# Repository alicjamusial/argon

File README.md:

# Argon & Benzene - SPI NOR Flash programmer & reader

### ◾ About the project

This project consists of two boards: **Argon** and **Benzene**.

 **Argon** is a SPI NOR flash programmer & reader. It's based on the FT2232H microcontroller (with two UARTs - A & B). The board has three LED indicators of data - on TX, RX and CS lines and some sockets to be able to plug in the logic analyzer. Version 1.0 of Argon is available [in the releases section](https://github.com/alicjamusial/argon/releases/tag/argon-1.0). 

<br>

 **Benzene** is a DIP-8/DIP-16 to Argon adapter. It includes mostly a few capacitors and resistors to allow SPI flash to run smoothly. There is also a 555 timer with LED indicator on CS line goldpins to attach the logic analyzer.
Version 1.0 of Benzene is available [in the releases section](https://github.com/alicjamusial/argon/releases/tag/benzene-1.0).

<br>
Argon works best with Benzene attached - they are designed to match each other (you can put two Benzene boards on top of the Argon). Argon can be also used separately as USB<->UART/FIFO/I2C/SPI converter (similar to FTDI Mini Module). 

Both boards were designed using [KiCad 5.1.6](https://kicad.org/).

### ◾ Software
Argon software is available in [this repository](https://github.com/alicjamusial/argon-driver).

### ◾ Known issues
**Argon 1.1**
- No known issues, but wasn't assembled yet.

**Benzene 1.0**
- Logo is too small and illegible (not very important, so won't be fixed by now)

**Project**
- KiCad libraries are a bit chaotic (not very important, so won't be fixed by now)

### ◾ Usage examples

Argon is meant to be used as SPI NOR flash reader & writer with:
- Benzene & flash soldered to DIP-8/DIP-16 board adapter
- Benzene & flash inside DIP-8/DIP-16 adapter
- Benzene & clip with DIP-8/16 adapter to read or program flash placed on another board

It can be also used standalone as USB<->UART/FIFO/I2C/SPI converter (all FTDI Mini Module functionalities in the nicer and more readable form).

Note: all photos show Argon in version 1.0.

### ◾ Schematics and designs
All of them can be found [in the releases section](https://github.com/alicjamusial/argon/releases) as KiCad files, gerber files, pdf and svg format.

#### ▪️ Argon 1.1

#### ▪️ Benzene 1.0

### ◾ Other hints
When assembling your own Argon or Benzene please use LED's resistors calculated for your chosen colours.

### ◾ License
Argon and Benzene are available on Creative Commons Attribution Share Alike 4.0 International license (more in [license file](LICENSE.txt)). You are free to use it, modify it and produce as many of your own boards as you need :)

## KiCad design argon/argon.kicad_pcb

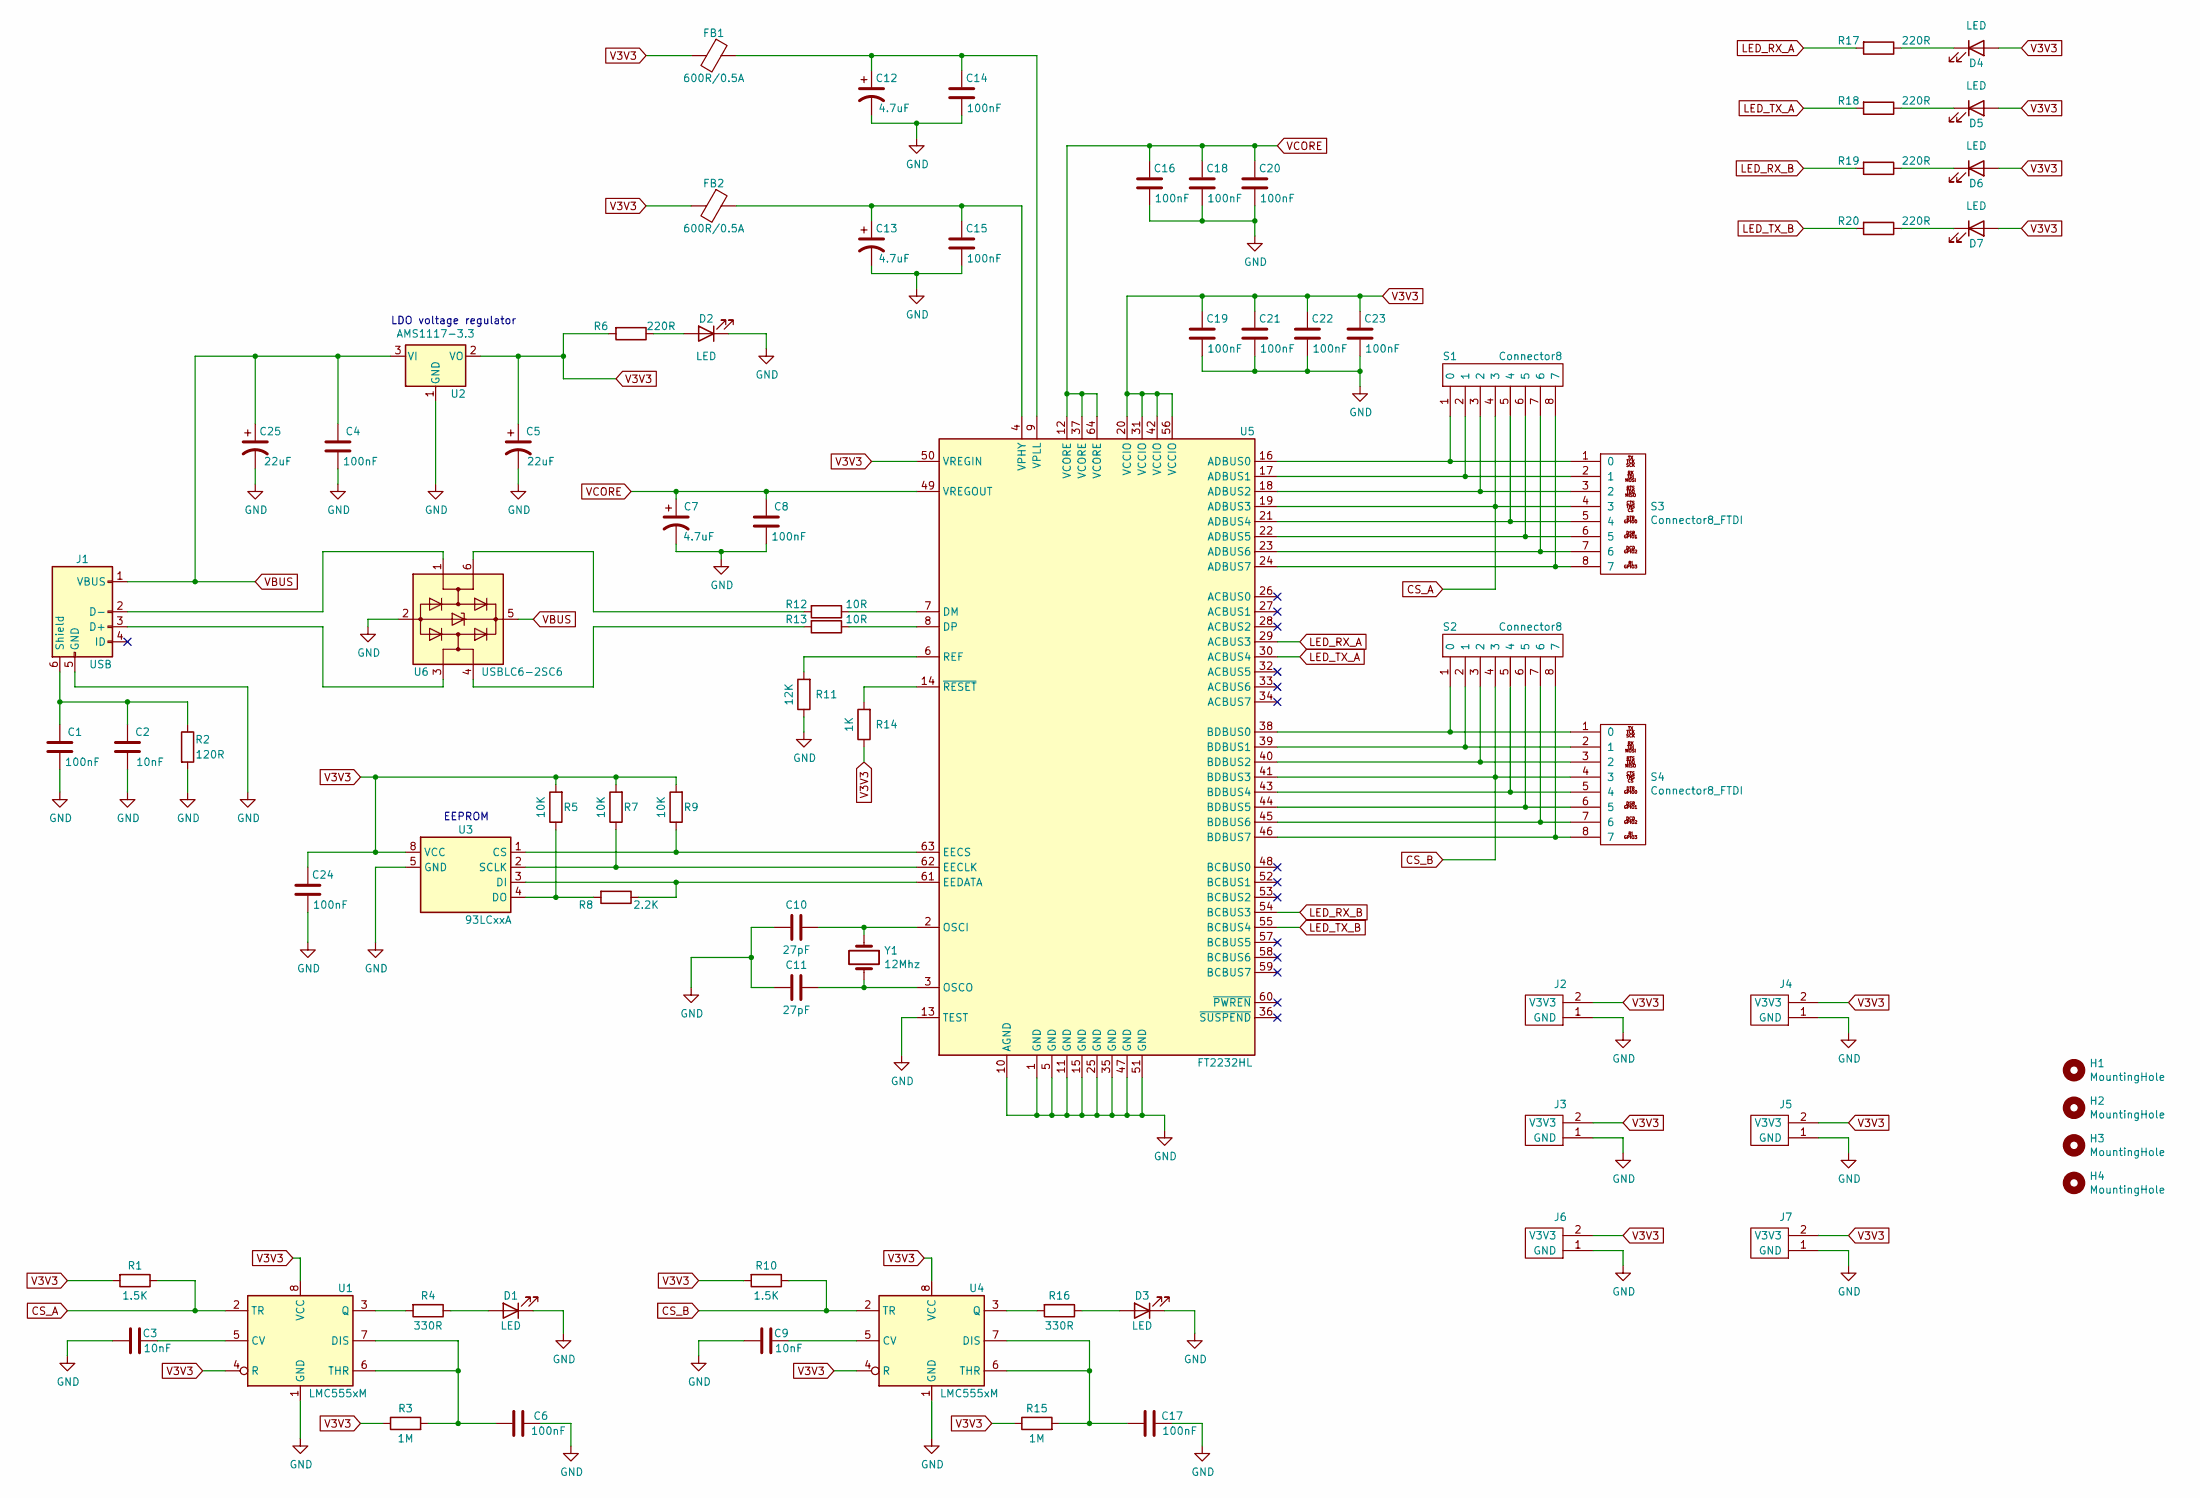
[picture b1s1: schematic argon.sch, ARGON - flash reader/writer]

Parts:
C1, C4, C6, C8, C14, C15, C16, C17, C18, C19, C20, C21, C22, C23, C24: 100nF; C_0603_1608Metric
C2, C3, C9: 10nF; C_0603_1608Metric
C5, C25: 22uF; CP_EIA-3216-18_Kemet-A
C7, C12, C13: 4.7uF; CP_EIA-3216-18_Kemet-A
C10, C11: 27pF; C_0603_1608Metric
D1, D2, D3, D4, D5, D6, D7: LED; LED_0805_2012Metric
FB1, FB2: 600R/0.5A; Murata-BLM18-0.15-t0.8-0-0-IPC_A
H1, H2, H3, H4: MountingHole; MountingHole_3.2mm_M3
J1: USB; USB_Mini-B_Wuerth_65100516121_Horizontal
J2, J3, J4, J5, J6, J7: V3V3-GND; PinHeader_1x02_P2.54mm_Vertical
R1, R10: 1.5K; R_0603_1608Metric
R2: 120R; R_0603_1608Metric
R3, R15: 1M; R_0603_1608Metric
R4, R16: 330R; R_0603_1608Metric
R5, R7, R9: 10K; R_0603_1608Metric
R6, R17, R18, R19, R20: 220R; R_0603_1608Metric
R8: 2.2K; R_0603_1608Metric
R11: 12K; R_0603_1608Metric
R12, R13: 10R; R_0603_1608Metric
R14: 1K; R_0603_1608Metric
S1, S2: Connector8; PinHeader_1x08_P2.54mm_Vertical
S3, S4: Connector8_FTDI; PinHeader_1x08_P2.54mm_Vertical
U1, U4: LMC555xM; VSSOP-8_3.0x3.0mm_P0.65mm
U2: AMS1117-3.3; SOT-223-3_TabPin2
U3: 93LCxxA; SOIC-8_3.9x4.9mm_P1.27mm
U5: FT2232HL; LQFP-64_10x10mm_P0.5mm
U6: USBLC6-2SC6; SOT-23-6
Y1: 12Mhz; Crystal_SMD_SeikoEpson_TSX3225-4Pin_3.2x2.5mm

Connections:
CS_A: R1.1, S1.4 (3), S3.4 (3), U1.2 (TR), U5.19 (ADBUS3)
CS_B: R10.1, S2.4 (3), S4.4 (3), U4.2 (TR), U5.41 (BDBUS3)
GND: C1.1, C2.1, C3.2, C4.2, C5.2, C6.2, C7.2, C8.1, C9.2, C10.2, C11.2, C12.2, C13.2, C14.1, C15.1, C16.1, C17.2, C18.1, C19.1, C20.1, C21.1, C22.1, C23.1, C24.1, C25.2, D1.1 (K), D2.1 (K), D3.1 (K), J1.5 (GND), J2.1 (GND), J3.1 (GND), J4.1 (GND), J5.1 (GND), J6.1 (GND), J7.1 (GND), R2.2, R11.1, U1.1 (GND), U2.1 (GND), U3.5 (GND), U4.1 (GND), U5.1 (GND), U5.5 (GND), U5.10 (AGND), U5.11 (GND), U5.13 (TEST), U5.15 (GND), U5.25 (GND), U5.35 (GND), U5.47 (GND), U5.51 (GND), U6.2 (GND)
LED_RX_A: R17.2, U5.29 (ACBUS3)
LED_RX_B: R19.2, U5.54 (BCBUS3)
LED_TX_A: R18.2, U5.30 (ACBUS4)
LED_TX_B: R20.2, U5.55 (BCBUS4)
unnamed: C1.2, C2.2, J1.6 (Shield), R2.1
unnamed: C3.1, U1.5 (CV)
unnamed: C6.1, R3.2, U1.6 (THR), U1.7 (DIS)
unnamed: C9.1, U4.5 (CV)
unnamed: C10.1, U5.2 (OSCI), Y1.1
unnamed: C11.1, U5.3 (OSCO), Y1.2
unnamed: C12.1, C14.2, FB1.1, U5.9 (VPLL)
unnamed: C13.1, C15.2, FB2.1, U5.4 (VPHY)
unnamed: C17.1, R15.2, U4.6 (THR), U4.7 (DIS)
unnamed: D1.2 (A), R4.1
unnamed: D2.2 (A), R6.1
unnamed: D3.2 (A), R16.1
unnamed: D4.1 (K), R17.1
unnamed: D5.1 (K), R18.1
unnamed: D6.1 (K), R19.1
unnamed: D7.1 (K), R20.1
unnamed: J1.2 (D-), U6.1 (I/O1)
unnamed: J1.3 (D+), U6.3 (I/O2)
unnamed: R4.2, U1.3 (Q)
unnamed: R5.1, R8.2, U3.4 (DO)
unnamed: R7.1, U3.2 (SCLK), U5.62 (EECLK)
unnamed: R8.1, U3.3 (DI), U5.61 (EEDATA)
unnamed: R9.1, U3.1 (CS), U5.63 (EECS)
unnamed: R11.2, U5.6 (REF)
unnamed: R12.1, U5.7 (DM)
unnamed: R12.2, U6.6 (I/O1)
unnamed: R13.1, U5.8 (DP)
unnamed: R13.2, U6.4 (I/O2)
unnamed: R14.2, U5.14 (~RESET)
unnamed: R16.2, U4.3 (Q)
unnamed: S1.1 (0), S3.1 (0), U5.16 (ADBUS0)
unnamed: S1.2 (1), S3.2 (1), U5.17 (ADBUS1)
unnamed: S1.3 (2), S3.3 (2), U5.18 (ADBUS2)
unnamed: S1.5 (4), S3.5 (4), U5.21 (ADBUS4)
unnamed: S1.6 (5), S3.6 (5), U5.22 (ADBUS5)
unnamed: S1.7 (6), S3.7 (6), U5.23 (ADBUS6)
unnamed: S1.8 (7), S3.8 (7), U5.24 (ADBUS7)
unnamed: S2.1 (0), S4.1 (0), U5.38 (BDBUS0)
unnamed: S2.2 (1), S4.2 (1), U5.39 (BDBUS1)
unnamed: S2.3 (2), S4.3 (2), U5.40 (BDBUS2)
unnamed: S2.5 (4), S4.5 (4), U5.43 (BDBUS4)
unnamed: S2.6 (5), S4.6 (5), U5.44 (BDBUS5)
unnamed: S2.7 (6), S4.7 (6), U5.45 (BDBUS6)
unnamed: S2.8 (7), S4.8 (7), U5.46 (BDBUS7)
V3V3: C5.1, C19.2, C21.2, C22.2, C23.2, C24.2, D4.2 (A), D5.2 (A), D6.2 (A), D7.2 (A), FB1.2, FB2.2, J2.2 (V3V3), J3.2 (V3V3), J4.2 (V3V3), J5.2 (V3V3), J6.2 (V3V3), J7.2 (V3V3), R1.2, R3.1, R5.2, R6.2, R7.2, R9.2, R10.2, R14.1, R15.1, U1.4 (R), U1.8 (VCC), U2.2 (VO), U3.8 (VCC), U4.4 (R), U4.8 (VCC), U5.20 (VCCIO), U5.31 (VCCIO), U5.42 (VCCIO), U5.50 (VREGIN), U5.56 (VCCIO)
VBUS: C4.1, C25.1, J1.1 (VBUS), U2.3 (VI), U6.5 (VBUS)
VCORE: C7.1, C8.2, C16.2, C18.2, C20.2, U5.12 (VCORE), U5.37 (VCORE), U5.49 (VREGOUT), U5.64 (VCORE)

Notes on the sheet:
LDO voltage regulator
EEPROM

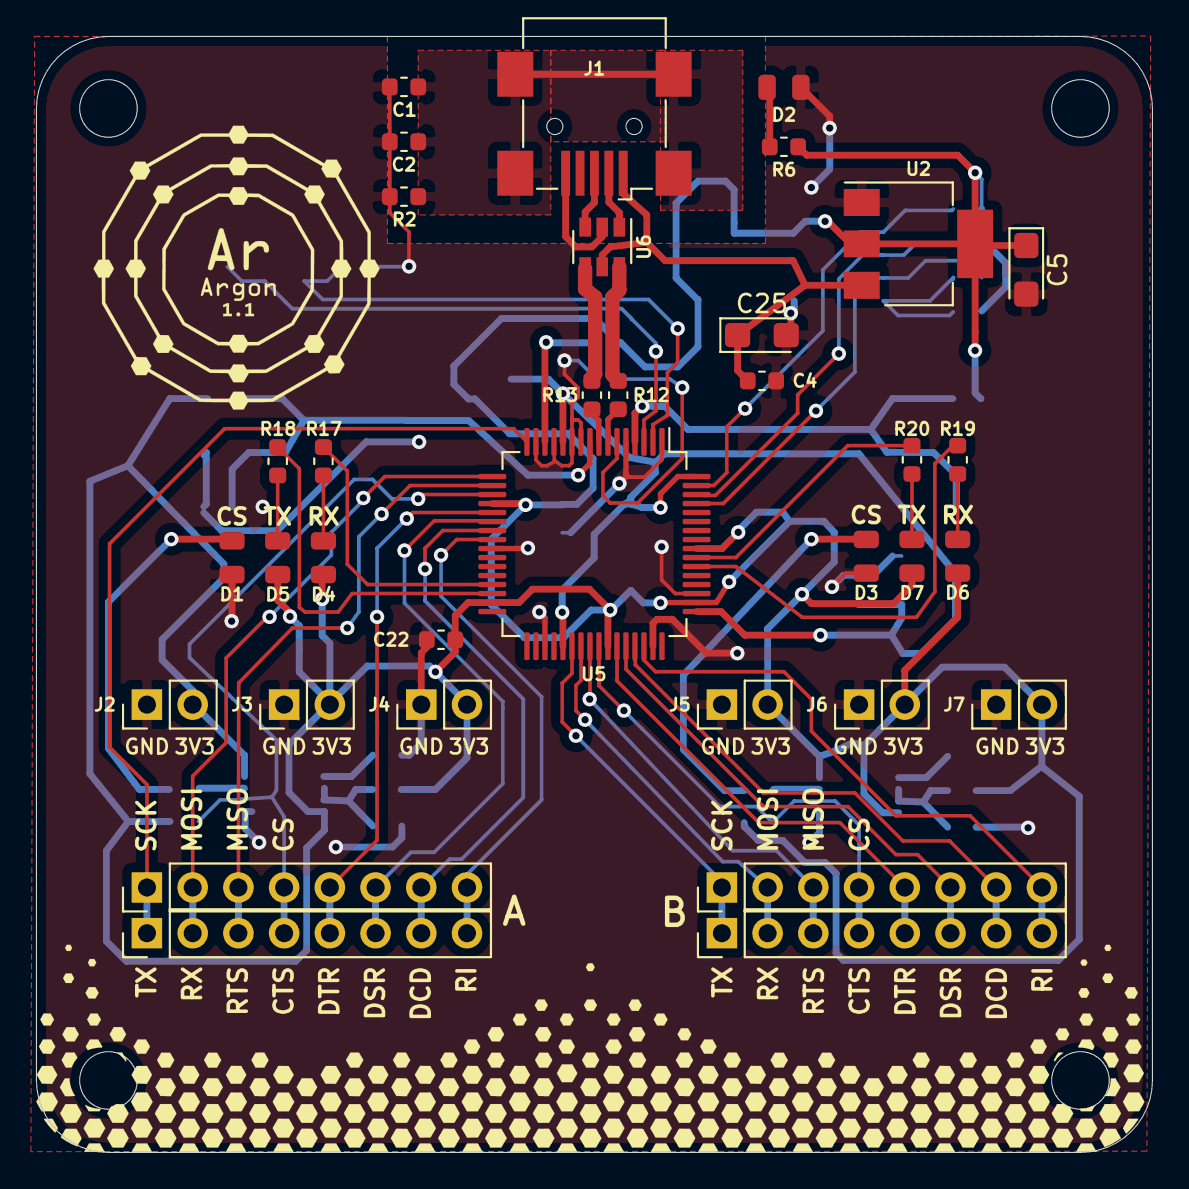
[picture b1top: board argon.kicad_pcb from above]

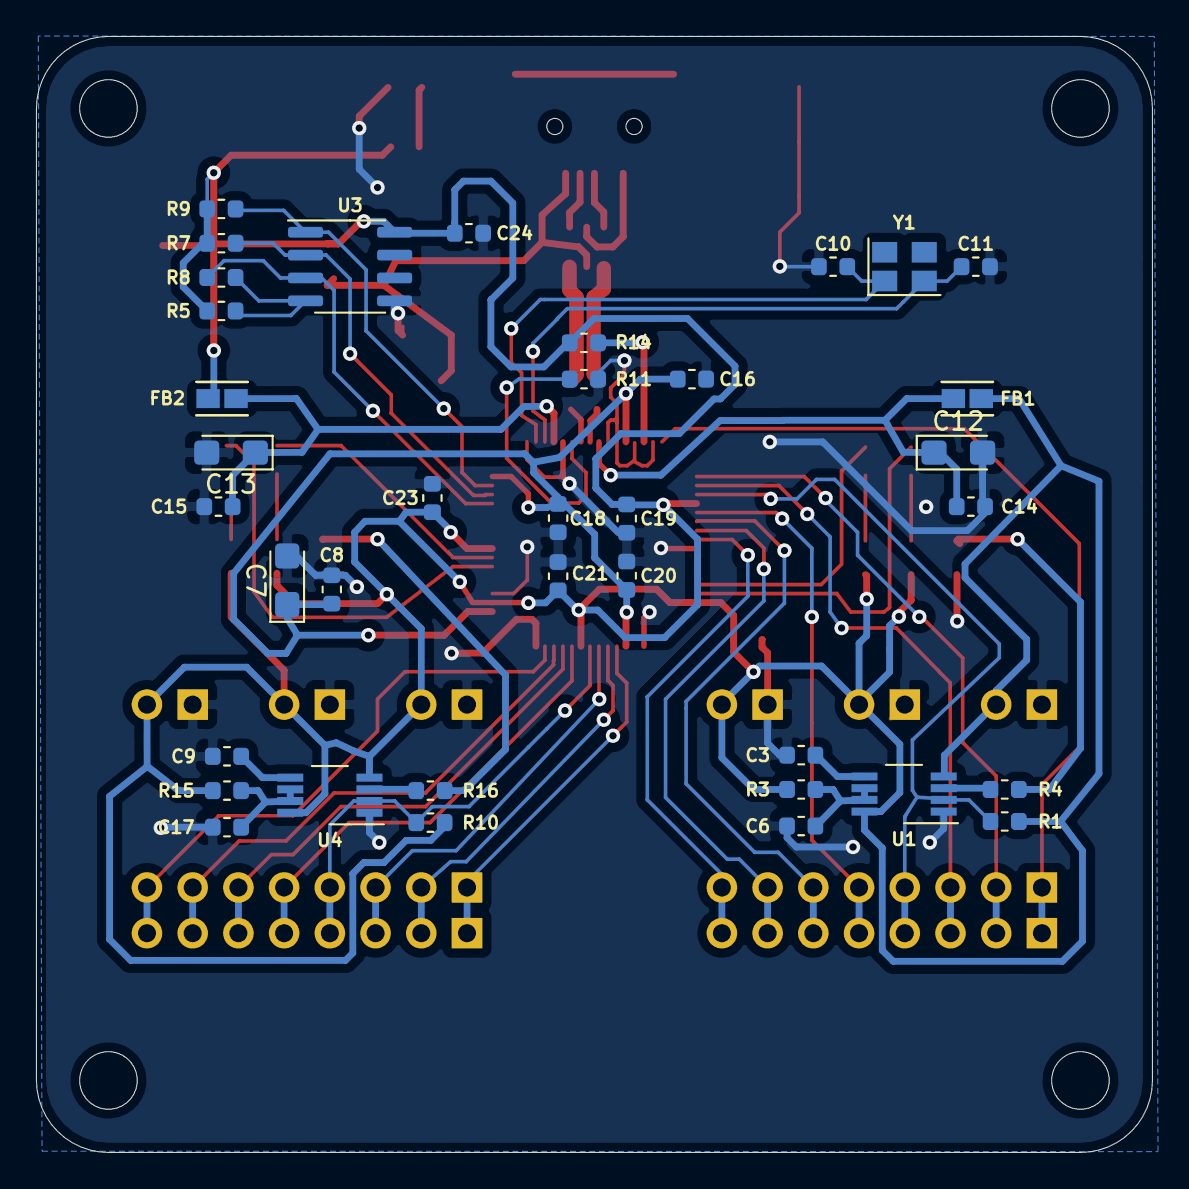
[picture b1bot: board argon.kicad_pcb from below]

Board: 2 copper layers, 62.0 x 62.0 mm, 76 parts (37 on the bottom side), 54 nets.

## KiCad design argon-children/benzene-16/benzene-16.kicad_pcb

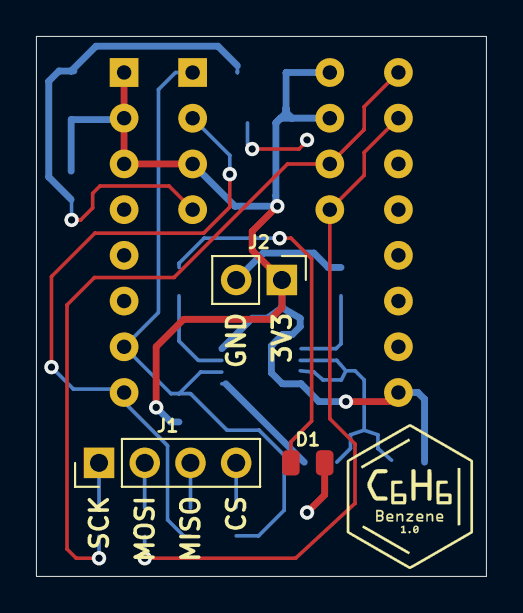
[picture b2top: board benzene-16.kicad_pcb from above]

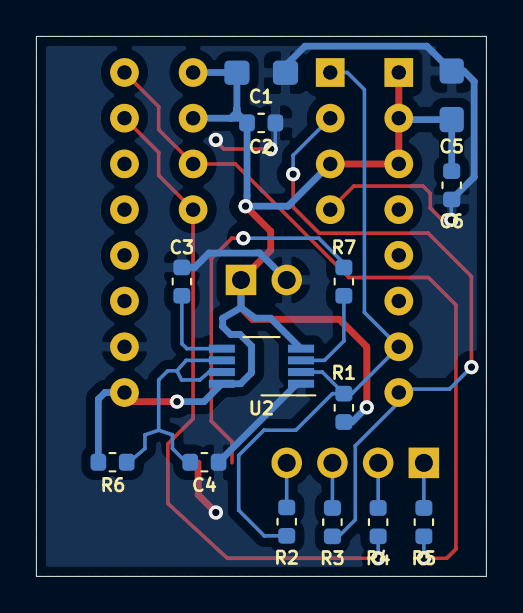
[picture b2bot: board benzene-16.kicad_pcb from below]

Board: 2 copper layers, 25.0 x 30.0 mm, 19 parts (14 on the bottom side), 14 nets.

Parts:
C1, C5: 10uF; CP_EIA-3216-18_Kemet-A
C2, C4, C6: 100nF; C_0603_1608Metric
C3: 10nF; C_0603_1608Metric
D1: LED; LED_0805_2012Metric
J1: Conn2; PinHeader_1x04_P2.54mm_Vertical
J2: Conn1; PinHeader_1x02_P2.54mm_Vertical
R1: 1.5K; R_0603_1608Metric
R2, R3, R4, R5: 47R; R_0603_1608Metric
R6: 1M; R_0603_1608Metric
R7: 330R; R_0603_1608Metric
U1: DIP-8; DIP-8_W7.62mm_Socket_wihtout_lines
U2: LMC555; VSSOP-8_3.0x3.0mm_P0.65mm
U3: DIP-16; DIP-16_W15.24mm_without_lines

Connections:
CS: R1.2, R2.1, U1.1, U2.2, U3.7
GND: C1.2, C2.1, C3.1, C4.2, C5.2, C6.1, D1.1, J2.2, U1.4, U2.1, U3.10
MISO: R3.1, U1.2, U3.8
MOSI: R4.1, U1.5, U3.15
unnamed: C3.2, U2.5
unnamed: C4.1, R6.2, U2.6, U2.7
unnamed: D1.2, R7.2
unnamed: J1.1, R5.2
unnamed: J1.2, R4.2
unnamed: J1.3, R3.2
unnamed: J1.4, R2.2
unnamed: R7.1, U2.3
SCK: R5.1, U1.6, U3.16
V3V3: C1.1, C2.2, C5.1, C6.2, J2.1, R1.1, R6.1, U1.3, U1.7, U1.8, U2.4, U2.8, U3.1, U3.2, U3.3, U3.9

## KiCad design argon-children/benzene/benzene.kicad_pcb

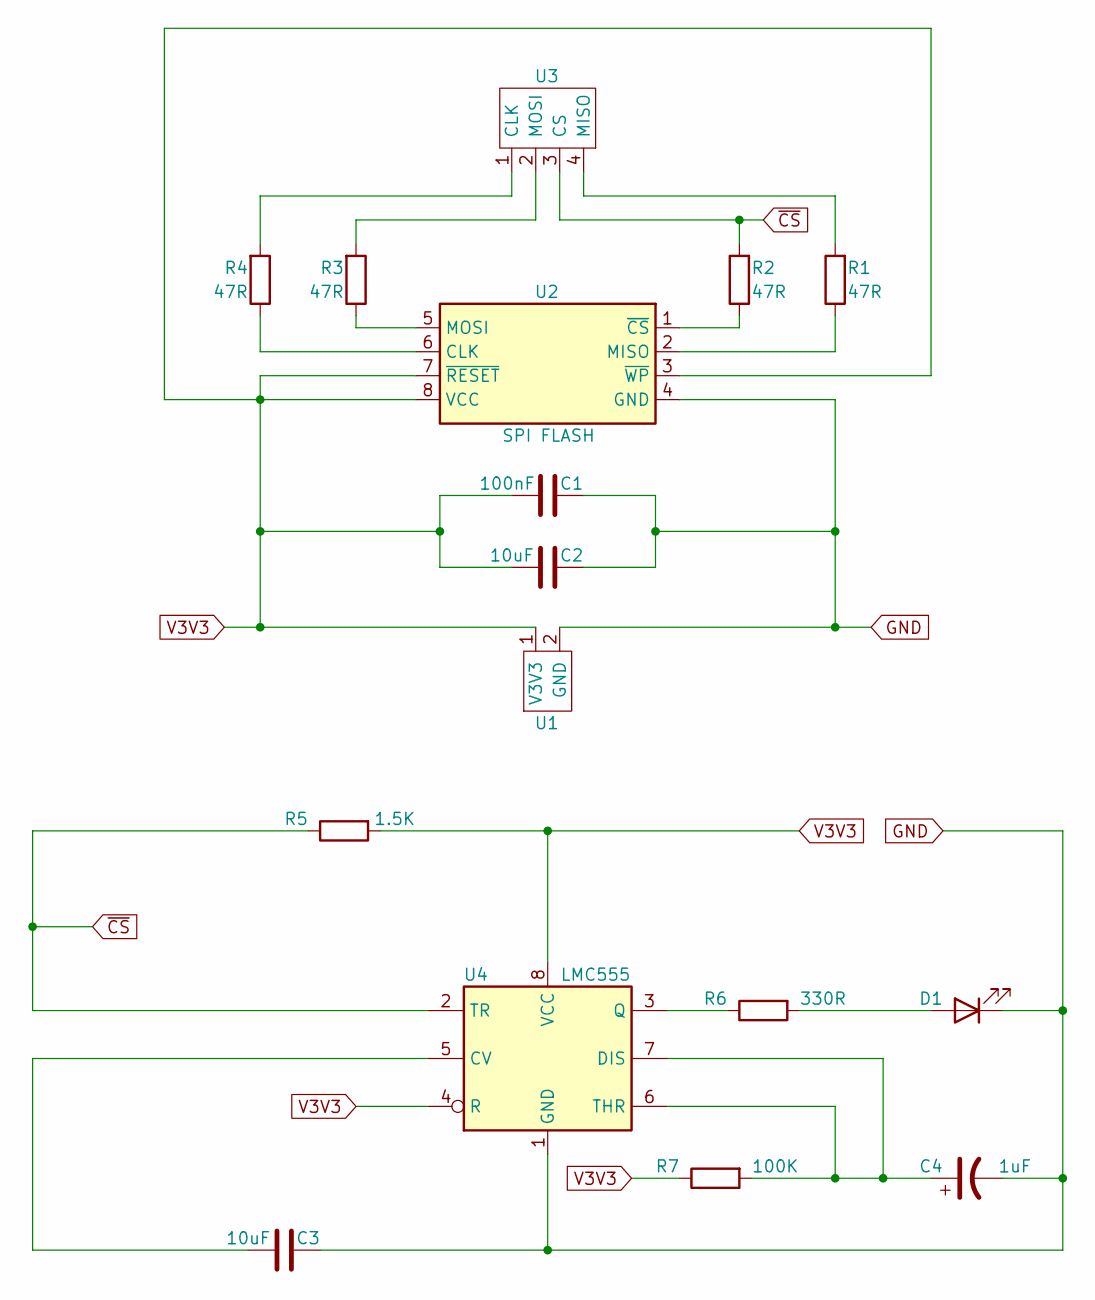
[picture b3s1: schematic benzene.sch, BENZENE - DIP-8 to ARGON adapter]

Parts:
C1: 100nF; C_0603_1608Metric
C2, C3: 10uF; C_0603_1608Metric
C4: 1uF; C_0603_1608Metric
D1: LED; LED_0805_2012Metric
R1, R2, R3, R4: 47R; R_0603_1608Metric
R5: 1.5K; R_0603_1608Metric
R6: 330R; R_0603_1608Metric
R7: 100K; R_0603_1608Metric
U1: Conn1; PinHeader_1x02_P2.54mm_Vertical
U2: SPI FLASH; DIP-8_W7.62mm_Socket
U3: Conn2; PinHeader_1x04_P2.54mm_Vertical
U4: LMC555; VSSOP-8_3.0x3.0mm_P0.65mm

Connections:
GND: C1.2, C2.2, C3.2, C4.2, D1.1 (K), U1.2 (GND), U2.4 (GND), U4.1 (GND)
unnamed: C3.1, U4.5 (CV)
unnamed: C4.1, R7.2, U4.6 (THR), U4.7 (DIS)
unnamed: D1.2 (A), R6.2
unnamed: R1.1, U2.2 (MISO)
unnamed: R1.2, U3.4 (MISO)
unnamed: R2.1, U2.1 (~CS)
unnamed: R3.1, U2.5 (MOSI)
unnamed: R3.2, U3.2 (MOSI)
unnamed: R4.1, U2.6 (CLK)
unnamed: R4.2, U3.1 (CLK)
unnamed: R6.1, U4.3 (Q)
V3V3: C1.1, C2.1, R5.2, R7.1, U1.1 (V3V3), U2.3 (~WP), U2.7 (~RESET), U2.8 (VCC), U4.4 (R), U4.8 (VCC)
~CS: R2.2, R5.1, U3.3 (CS), U4.2 (TR)

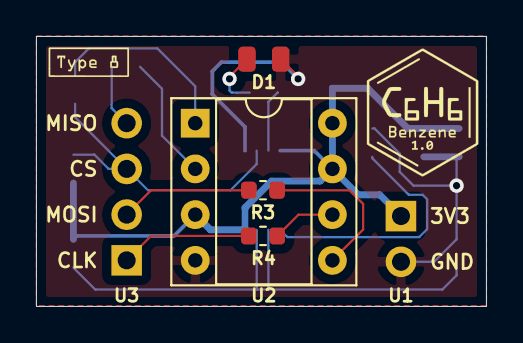
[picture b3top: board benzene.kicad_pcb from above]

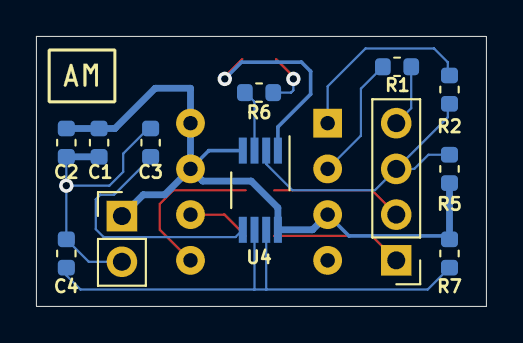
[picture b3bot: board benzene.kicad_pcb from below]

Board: 2 copper layers, 25.0 x 15.0 mm, 16 parts (12 on the bottom side), 14 nets.

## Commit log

2020-12-01 Repo init
2020-12-06 Add USB and oscillator
2020-12-06 Add EEPROM & fix libs
2020-12-06 Place 555
2020-12-08 Add 555
2020-12-08 Add LDO
2020-12-11 Add benzene-8
2020-12-11 Add 555 to benzene
2020-12-11 Benzene & 555 - redraw to two schemas
2020-12-11 Benzene footprints
2020-12-12 Benzene - PCB, part 1
2020-12-12 Benzene - part 2 PCB
2020-12-12 Benzene - verson with logo and centered 2 pins
2020-12-12 Add logos & author
2020-12-12 Benzene prealpha
2020-12-13 Benzene
2020-12-13 25x15 - part1
2020-12-13 Benzene refactored
2020-12-13 Benzene 16
2020-12-13 Chaotic evil - argon, benzen, some random freecad
2020-12-14 Argon USB & custom footprint for DIP-16
2020-12-18 Aegon USB and power
2020-12-18 More voltages
2020-12-18 Leds & structure
2020-12-18 Fix bugs
2020-12-18 Final schematic
2020-12-18 Add FBs and start positioning buses on PCB
2020-12-19 Clear folders
2020-12-19 PCB - part 1
2020-12-19 Argon PCB - part 2 + logo
2020-12-19 Change some capacitors to tantals
2020-12-19 PCB 6x6cm
2020-12-19 PCB - chaotic
2020-12-19 10.16mm between sockets on argon & benzene
2020-12-20 Argon PCB
2020-12-20 Piotrek's review
2020-12-22 Argon & beznen compatible
2020-12-22 Argon - all elements and start paths
2020-12-22 Smaller argon
2020-12-22 5x6cm
2020-12-22 PCB wip
2020-12-22 Add 0.8 path for usb
2020-12-23 USB design
2020-12-23 Bigger logo & move resistors
2020-12-23 555 routes
2020-12-23 FBs routing
2020-12-23 TX & RX leds and A pads
2020-12-23 V1.8 & V3.3
2020-12-23 Move all up to avoid holes overlapping
2020-12-23 EEPROM routing
2020-12-23 Ground and paths
2020-12-23 Missing paths
2020-12-23 All routes
2020-12-23 Add capacitor footprint without lines
2020-12-23 Final touch
2020-12-23 Sizes
2020-12-23 GND on front & fix paths
2020-12-23 Move capacitor & add filled zone near USB
2020-12-23 Fix connected pins on ftdi
2020-12-23 Add labels
2020-12-23 Small paths adjustments
2020-12-23 Rounded corners
2020-12-23 Move everything to make more place for labels
2020-12-23 Benzene schematic
2020-12-24 Benzene schematic - final
2020-12-24 Benzene pcb
2020-12-25 Fix argon clearance & benzen step
2020-12-25 Fix benzene bug (gnd & 3v3)
2020-12-25 Export elements to xml
2020-12-25 Final touches
2020-12-25 Remove old benzene design
2021-01-13 Argon boards
2021-01-24 Argon v 1.0
2021-01-24 Benzene 1.0
2021-01-24 Add readme and license
2021-01-24 Add images
2021-01-24 Fix incorrectly designed LEDs
2021-01-24 Resize board to 62mm, update logo & add pattern
2021-01-24 Argon 1.1
2021-02-07 Add link to software repo
2021-11-08 Update README.md
    https://forum.kicad.info/t/warning-avoid-all-links-to-kicad-pcb-org-use-kicad-org/31521
